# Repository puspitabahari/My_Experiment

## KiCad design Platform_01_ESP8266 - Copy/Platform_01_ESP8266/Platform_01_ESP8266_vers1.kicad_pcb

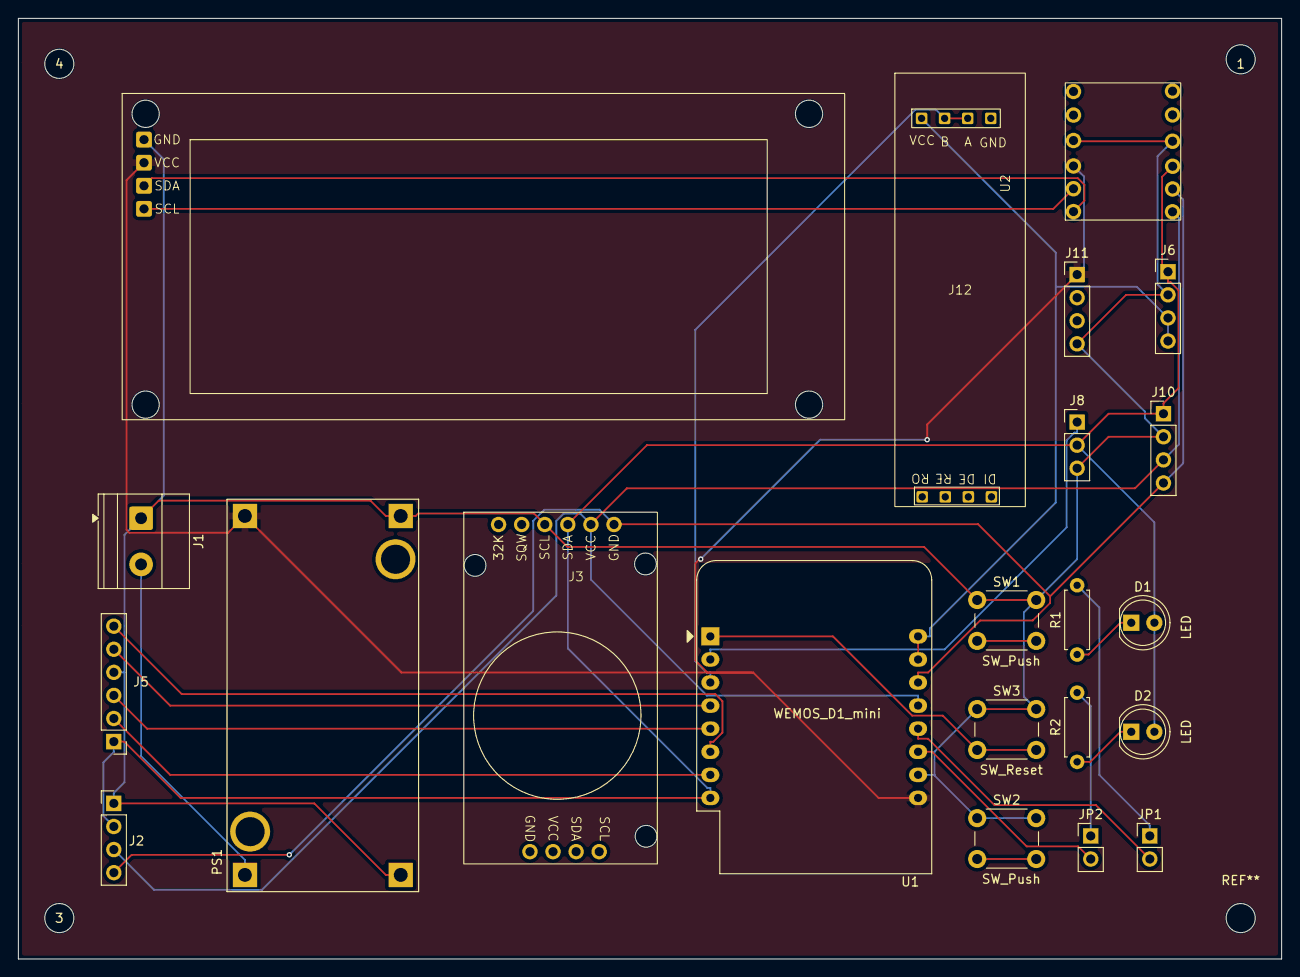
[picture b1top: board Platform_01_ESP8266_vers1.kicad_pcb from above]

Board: 2 copper layers, 139.0 x 103.5 mm, 25 parts (0 on the bottom side), 22 nets.

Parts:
1, 3, 4: MountingHole_3.2mm_M3
D1, D2: LED; LED_D5.0mm
J1: POWER_IN; TerminalBlock_Phoenix_MKDS-1,5-2-5.08_1x02_P5.08mm_Horizont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
J2: I2C_Port; PinHeader_1x04_P2.54mm_Vertical
J3: RTC; RTC_DS3231_Module
J4: LCD; LCDI2C_Module
J5: SPI; PinHeader_1x06_P2.54mm_Vertical
J6: SERIAL_PORT; PinHeader_1x04_P2.54mm_Vertical
J8: ADC_PORT; PinHeader_1x03_P2.54mm_Vertical
J10: J_PCF8574; PinHeader_1x04_P2.54mm_Vertical
J11: SISI_BUS; PinHeader_1x04_P2.54mm_Vertical
J12: SISI_LOGIC; RS485_Footprint
JP1, JP2: SolderJumper_2_Open; PinHeader_1x02_P2.54mm_Vertical
PS1: LM2596_Module; CONV_MC00100
R1, R2: 220; R_Axial_DIN0207_L6.3mm_D2.5mm_P7.62mm_Horizontal
SW1, SW2: SW_Push; SW_PUSH_6mm_H5mm
SW3: SW_Reset; SW_PUSH_6mm_H5mm
U1: WEMOS_D1_mini; WEMOS_D1_mini_light
U2: level_converter

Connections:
+3V3: D1.2 (A), D2.2 (A), J2.2, J3.3, J5.1, J6.1, J8.2, J10.1, U1.8 (3V3), U2.9 (LV)
+5V: J4.2, J11.1, PS1.OUT+, U1.9 (5V), U2.3 (HV)
/<NO NET>: SW3.2, U1.1 (~RST)
/ADC_A0: J8.1, U1.2 (A0)
/I2C_SCL: J2.4, J3.1, J10.4, U1.14 (SCL/D1), U2.8 (LV2)
/I2C_SDA: J2.3, J3.2, J10.3, U1.13 (SDA/D2), U2.7 (LV1)
/LCD_SCL_5V: J4.4, U2.2 (HV2)
/LCD_SDA_5V: J4.3, U2.1 (HV1)
/LED1_CTRL: JP1.2 (B), U1.12 (D3)
/LED2_CTRL: JP2.2 (B), U1.11 (D4)
/POWER_IN+: J1.2, PS1.IN+
/RS485_EN: J12.2, J12.3, U1.3 (D0)
/SPI_CS: J5.2, U1.7 (CS/D8)
/SPI_MISO: J5.3, U1.5 (MISO/D6)
/SPI_MOSI: J5.6, U1.6 (MOSI/D7)
/SPI_SCK: J5.5, U1.4 (SCK/D5)
/UART_RX: J6.3, J6.4, J12.1, U1.15 (RX), U1.16 (TX)
GND: J1.1, J2.1, J3.4, J4.1, J5.4, J6.2, J8.3, J10.2, J11.4, PS1.IN-, PS1.OUT-, SW1.1, SW2.1, SW3.1, U1.10 (GND), U2.4 (GND), U2.10 (GND)
unnamed: D1.1 (K), R1.1
unnamed: D2.1 (K), R2.1
unnamed: JP1.1 (A), R1.2
unnamed: JP2.1 (A), R2.2
